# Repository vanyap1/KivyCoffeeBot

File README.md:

# KivyCoffeeBot
Automatic coffee machine, based on arm or x86 pc.

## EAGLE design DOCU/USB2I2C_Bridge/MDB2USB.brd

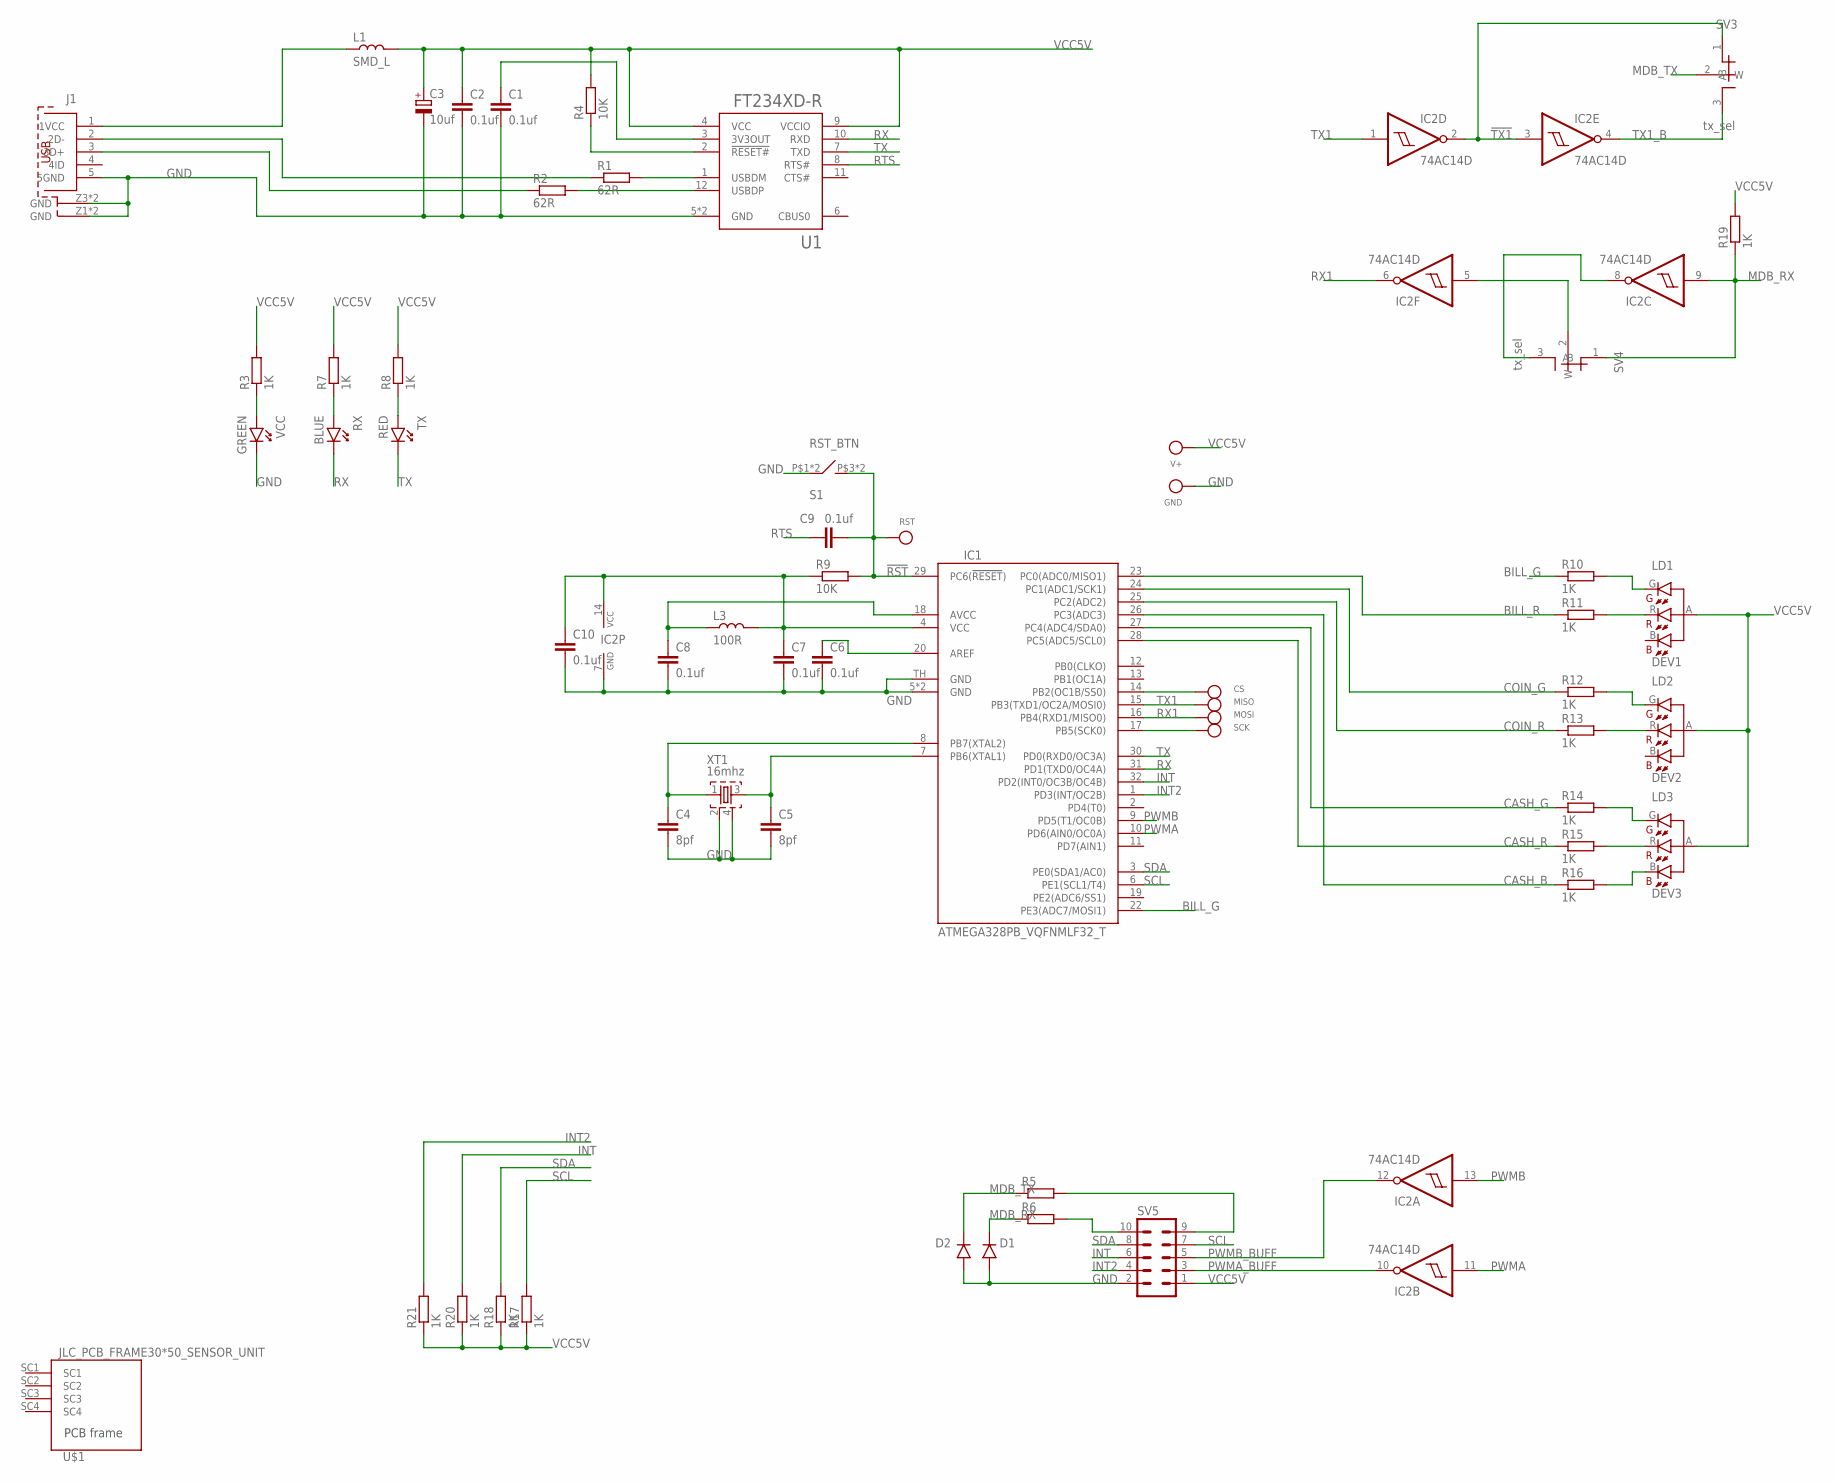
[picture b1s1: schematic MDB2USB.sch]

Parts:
C1, C2, C6, C7, C8, C9, C10: 0.1uf; 0603
C3: 10uf; KA-3528ASYC
C4, C5: 8pf; 0603
CS: TEST_POINT_D2MM; TP
D1, D2: D_MBRA340G; SMA403D
GND: TEST_POINT_D2MM; TP
IC1: ATMEGA328PB_VQFNMLF32_T; MLF32-TH
IC2: 74AC14D; SO14
J1: MINI_USB_TYP_B_@; 65100516121
L1: SMD_L; 0805
L3: 100R; 0603
LD1: DEV1; LTSN-N213EGBW
LD2: DEV2; LTSN-N213EGBW
LD3: DEV3; LTSN-N213EGBW
MISO: TEST_POINT_D2MM; TP
MOSI: TEST_POINT_D2MM; TP
R1, R2: 62R; 0603
R3, R7, R8, R10, R11, R12, R13, R14, R15, R16, R17, R18, R19, R20, R21: 1K; 0603
R4, R9: 10K; 0603
R5, R6: SMD_R1206; 1206
RST: TEST_POINT_D2MM; TP
RX: BLUE; 0603_P
S1: RST_BTN; GALILEO_VERT_BTN
SCK: TEST_POINT_D2MM; TP
SV3, SV4: tx_sel; 0603_JUMP
SV5: MA05-2
TX: RED; 0603_P
U1: FT234XD-R; IC_FT234XD-R
U$1: JLC_PCB_FRAME30*50_SENSOR_UNIT; 30X50_SENSOR_UNIT
V+: TEST_POINT_D2MM; TP
VCC: GREEN; 0603_P
XT1: 16mhz; QUARTZ_3X3MM

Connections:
!RST: C9.2, IC1.29 (PC6(!RESET!)), R9.2, RST.P$1, S1.P$3 (4), S1.P$4 (4)
!TX1: IC2.2 (O), IC2.3 (I), SV3.1 (A)
AREF: C6.1, IC1.20 (AREF)
AVCC: C8.1, IC1.18 (AVCC), L3.1
BILL_G: IC1.22 (PE3(ADC7/MOSI1)), R10.1
BILL_R: IC1.23 (PC0(ADC0/MISO1)), R11.1
CASH_B: IC1.26 (PC3(ADC3)), R16.1
CASH_G: IC1.27 (PC4(ADC4/SDA0)), R14.1
CASH_R: IC1.28 (PC5(ADC5/SCL0)), R15.1
COIN_G: IC1.24 (PC1(ADC1/SCK1)), R12.1
COIN_R: IC1.25 (PC2(ADC2)), R13.1
GND: C1.2, C2.2, C3.M (-), C4.2, C5.2, C6.2, C7.2, C8.2, C10.2, D1.P$2 (A), D2.P$2 (A), GND.P$1, IC1.5 (GND), IC1.21 (GND), IC1.TH (GND), IC2.7 (GND), J1.5 (5GND), J1.Z1 (GND), J1.Z2 (GND), J1.Z3 (GND), J1.Z4 (GND), S1.P$1 (1), S1.P$2 (1), SV5.2, U1.5 (GND), U1.13 (GND), VCC.1 (K), XT1.2, XT1.4
INT: IC1.32 (PD2(INT0/OC3B/OC4B)), R20.2, SV5.6
INT2: IC1.1 (PD3(INT/OC2B)), R21.2, SV5.4
MDB_RX: D2.P$1 (C), IC2.9 (I), R6.1, R19.1, SV4.1 (A)
MDB_TX: D1.P$1 (C), R5.1, SV3.2 (W)
unnamed: J1.1 (1VCC), L1.1
unnamed: J1.2 (2D-), R1.1
unnamed: J1.3 (3D+), R2.1
unnamed: R4.1, U1.2 (!RESET#)
unnamed: R2.2, U1.12 (USBDP)
unnamed: R1.2, U1.1 (USBDM)
unnamed: C1.1, U1.3 (3V3OUT)
unnamed: R3.1, VCC.2 (A)
unnamed: C4.1, IC1.8 (PB7(XTAL2)), XT1.1
unnamed: C5.1, IC1.7 (PB6(XTAL1)), XT1.3
unnamed: IC2.5 (I), SV4.2 (W)
unnamed: R7.1, RX.2 (A)
unnamed: R8.1, TX.2 (A)
unnamed: IC2.8 (O), SV4.3 (B)
unnamed: LD1.G (GC), R10.2
unnamed: LD1.R (RC), R11.2
unnamed: LD2.G (GC), R12.2
unnamed: LD2.R (RC), R13.2
unnamed: LD3.G (GC), R14.2
unnamed: LD3.R (RC), R15.2
unnamed: LD3.B (BC), R16.2
unnamed: CS.P$1, IC1.14 (PB2(OC1B/SS0))
unnamed: R6.2, SV5.10
unnamed: R5.2, SV5.9
PWMA: IC1.10 (PD6(AIN0/OC0A)), IC2.11 (I)
PWMA_BUFF: IC2.10 (O), SV5.3
PWMB: IC1.9 (PD5(T1/OC0B)), IC2.13 (I)
PWMB_BUFF: IC2.12 (O), SV5.5
RTS: C9.1, U1.8 (RTS#)
RX: IC1.31 (PD1(TXD0/OC4A)), RX.1 (K), U1.10 (RXD)
RX1: IC1.16 (PB4(RXD1/MISO0)), IC2.6 (O), MOSI.P$1
SCK: IC1.17 (PB5(SCK0)), SCK.P$1
SCL: IC1.6 (PE1(SCL1/T4)), R17.2, SV5.7
SDA: IC1.3 (PE0(SDA1/AC0)), R18.2, SV5.8
TX: IC1.30 (PD0(RXD0/OC3A)), TX.1 (K), U1.7 (TXD)
TX1: IC1.15 (PB3(TXD1/OC2A/MOSI0)), IC2.1 (I), MISO.P$1
TX1_B: IC2.4 (O), SV3.3 (B)
VCC5V: C2.1, C3.P (+), C7.1, C10.1, IC1.4 (VCC), IC2.14 (VCC), L1.2, L3.2, LD1.A, LD2.A, LD3.A, R3.2, R4.2, R7.2, R8.2, R9.1, R17.1, R18.1, R19.2, R20.1, R21.1, SV5.1, U1.4 (VCC), U1.9 (VCCIO), V+.P$1

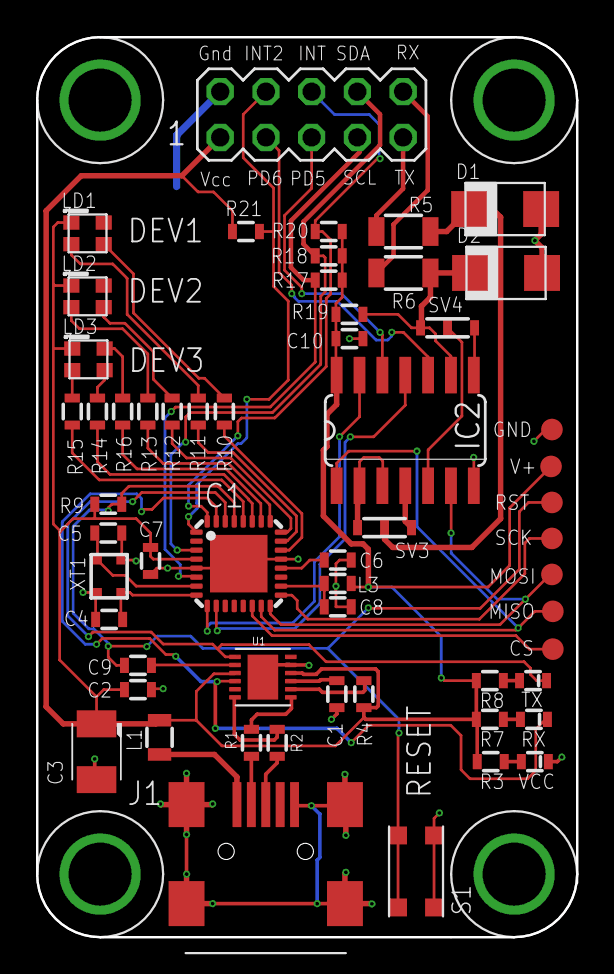
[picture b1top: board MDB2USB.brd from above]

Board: 2 copper layers, 30.0 x 50.0 mm, 58 parts (0 on the bottom side), 54 nets.

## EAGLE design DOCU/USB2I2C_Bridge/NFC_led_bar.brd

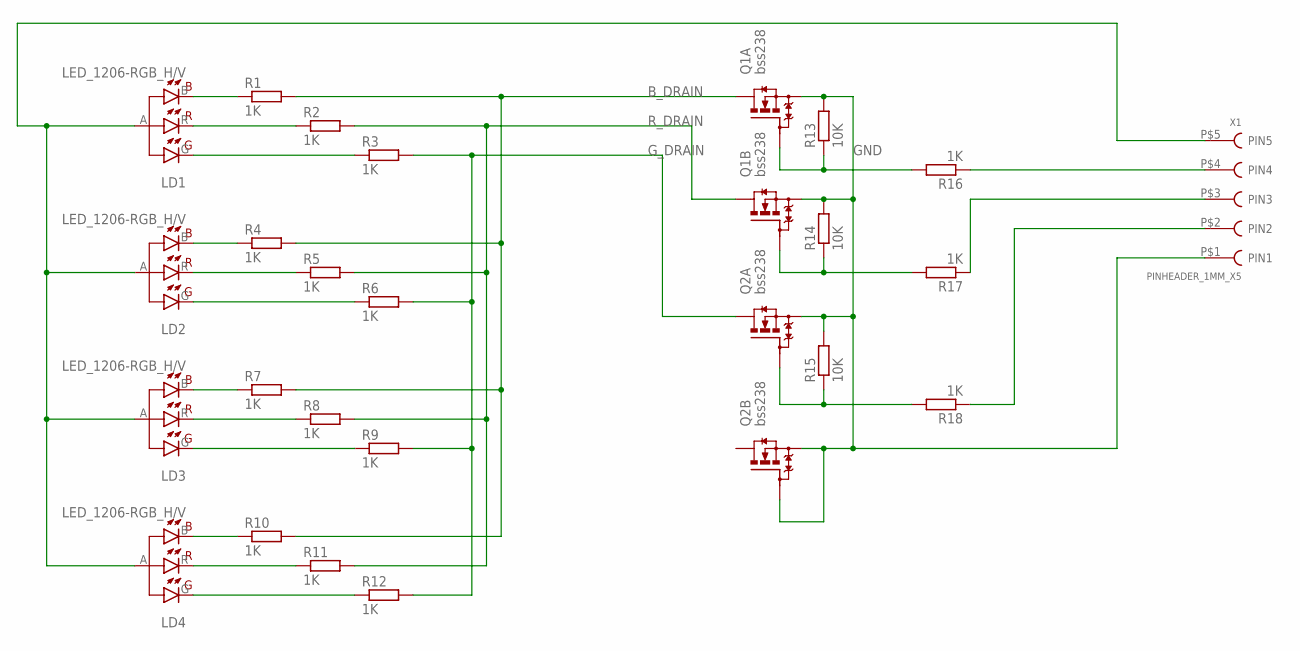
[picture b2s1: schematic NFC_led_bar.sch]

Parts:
LD1, LD2, LD3, LD4: LED_1206-RGB_H/V; RGB_1206_LED
Q1, Q2: bss238; SOT363
R1, R2, R3, R4, R5, R6, R7, R8, R9, R10, R11, R12, R16, R17, R18: 1K; 0603
R13, R14, R15: 10K; 0603
X1: PINHEADER_1MM_X5; PIN_1MM_X5

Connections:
B_DRAIN: Q1.6 (D), R1.2, R4.2, R7.2, R10.2
GND: Q1.1 (S), Q1.4 (S), Q2.1 (S), Q2.4 (S), Q2.5 (G), R13.2, R14.2, R15.2, X1.P$1 (PIN1)
G_DRAIN: Q2.6 (D), R3.2, R6.2, R9.2, R12.2
unnamed: LD1.A, LD2.A, LD3.A, LD4.A, X1.P$5 (PIN5)
unnamed: Q1.2 (G), R13.1, R16.2
unnamed: LD1.B (BC), R1.1
unnamed: LD1.R (RC), R2.1
unnamed: LD1.G (GC), R3.1
unnamed: LD2.B (BC), R4.1
unnamed: LD2.R (RC), R5.1
unnamed: LD2.G (GC), R6.1
unnamed: LD3.B (BC), R7.1
unnamed: LD3.R (RC), R8.1
unnamed: LD3.G (GC), R9.1
unnamed: LD4.B (BC), R10.1
unnamed: LD4.R (RC), R11.1
unnamed: LD4.G (GC), R12.1
unnamed: Q1.5 (G), R14.1, R17.2
unnamed: Q2.2 (G), R15.1, R18.2
unnamed: R16.1, X1.P$4 (PIN4)
unnamed: R17.1, X1.P$3 (PIN3)
unnamed: R18.1, X1.P$2 (PIN2)
R_DRAIN: Q1.3 (D), R2.2, R5.2, R8.2, R11.2

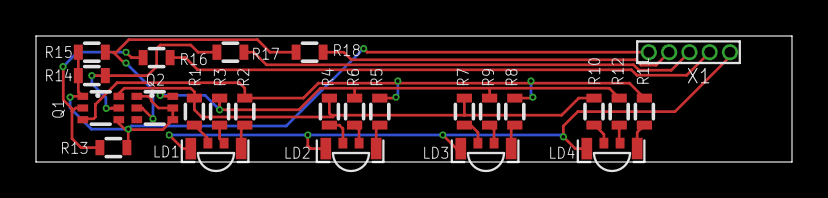
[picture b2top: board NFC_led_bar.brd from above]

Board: 2 copper layers, 42.0 x 7.0 mm, 25 parts (0 on the bottom side), 23 nets.

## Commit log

2024-04-16 Created kivy GUI
2024-04-17 added usb to i2c controller related data
2024-04-18 usb2i2c adapter serial listener and data parcer
